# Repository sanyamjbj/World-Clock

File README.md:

# World_Clock_8085
An Intel 8085 microprocessor based device displaying the time of all the geographical time zones based on a user input.<br/>

Main_code.asm --------> The 8085 assembly language program.<br/>
Peripheral.brd -------> Board layout file for the I/O board. <br/>
Peripheral.sch -------> Circuit Schematic file for I/O board. <br/>
CPU.brd --------------> Board layout file for the 8085 CPU board. <br/>
world_clock_2.0.sch --> Circuit Schematic file for the 8085 CPU board. <br/>
All board and schematic files are made using Autodesk EAGLE. <br/>

[Image (a) of the Device](https://drive.google.com/file/d/1ZphsaR_vkj9hESxW5N7R6vfBDCEByzWG/view?usp=sharing)

[Image (b) of the Device](https://drive.google.com/file/d/1xtrZFzuJcVHUMF8EjI57J5fJ46bng3HB/view?usp=sharing)

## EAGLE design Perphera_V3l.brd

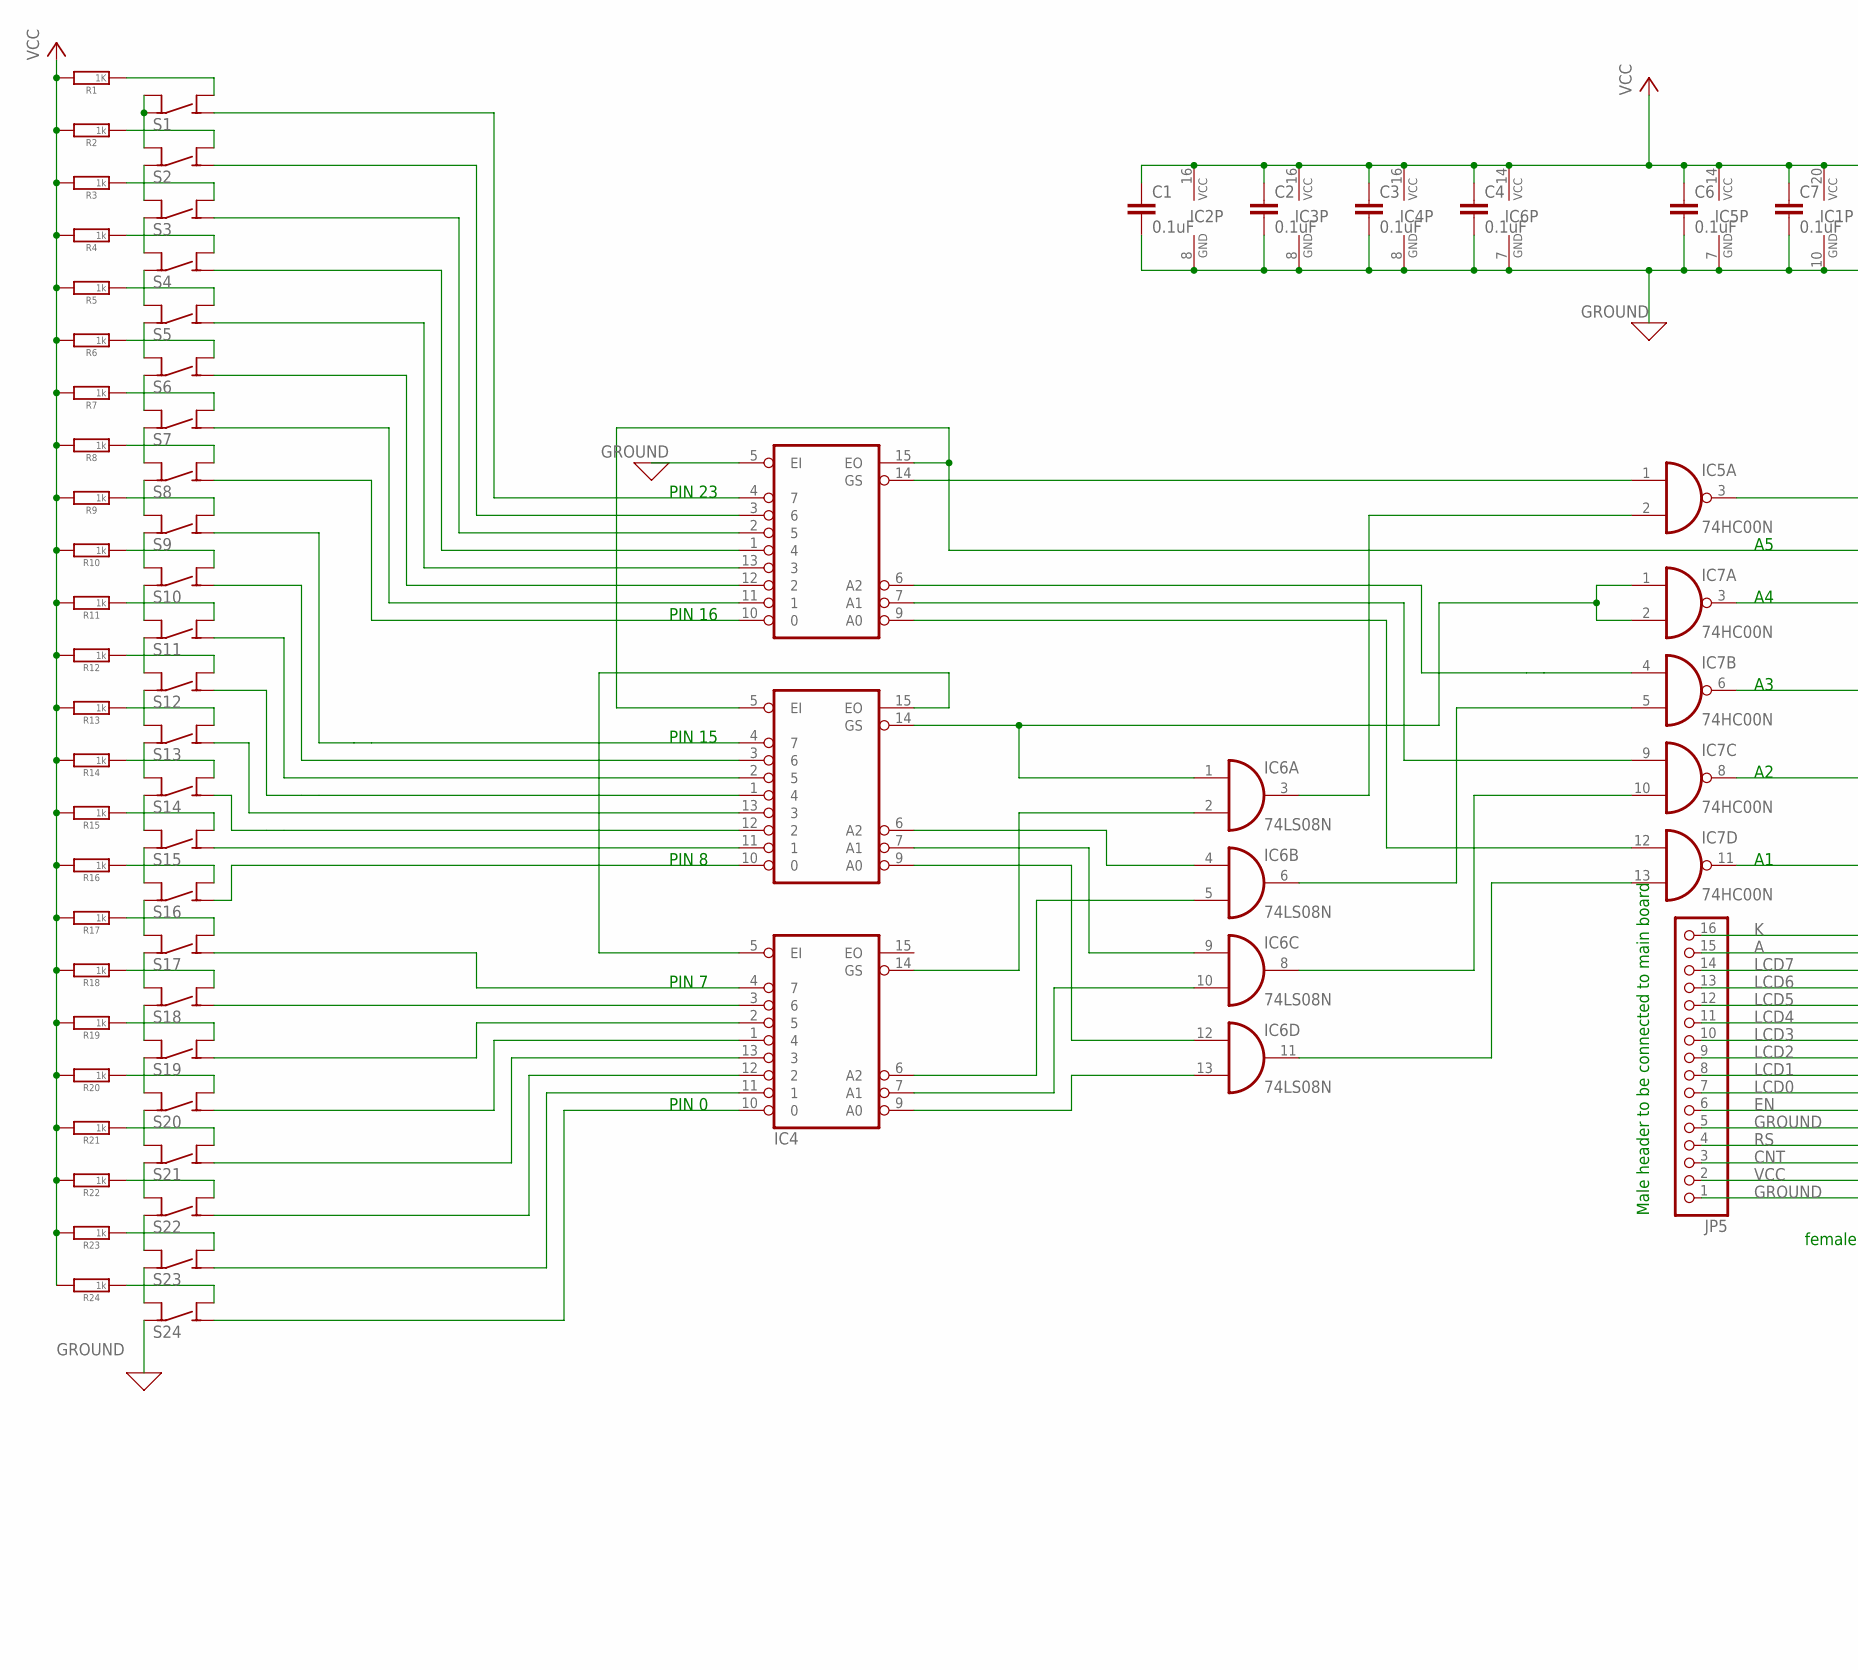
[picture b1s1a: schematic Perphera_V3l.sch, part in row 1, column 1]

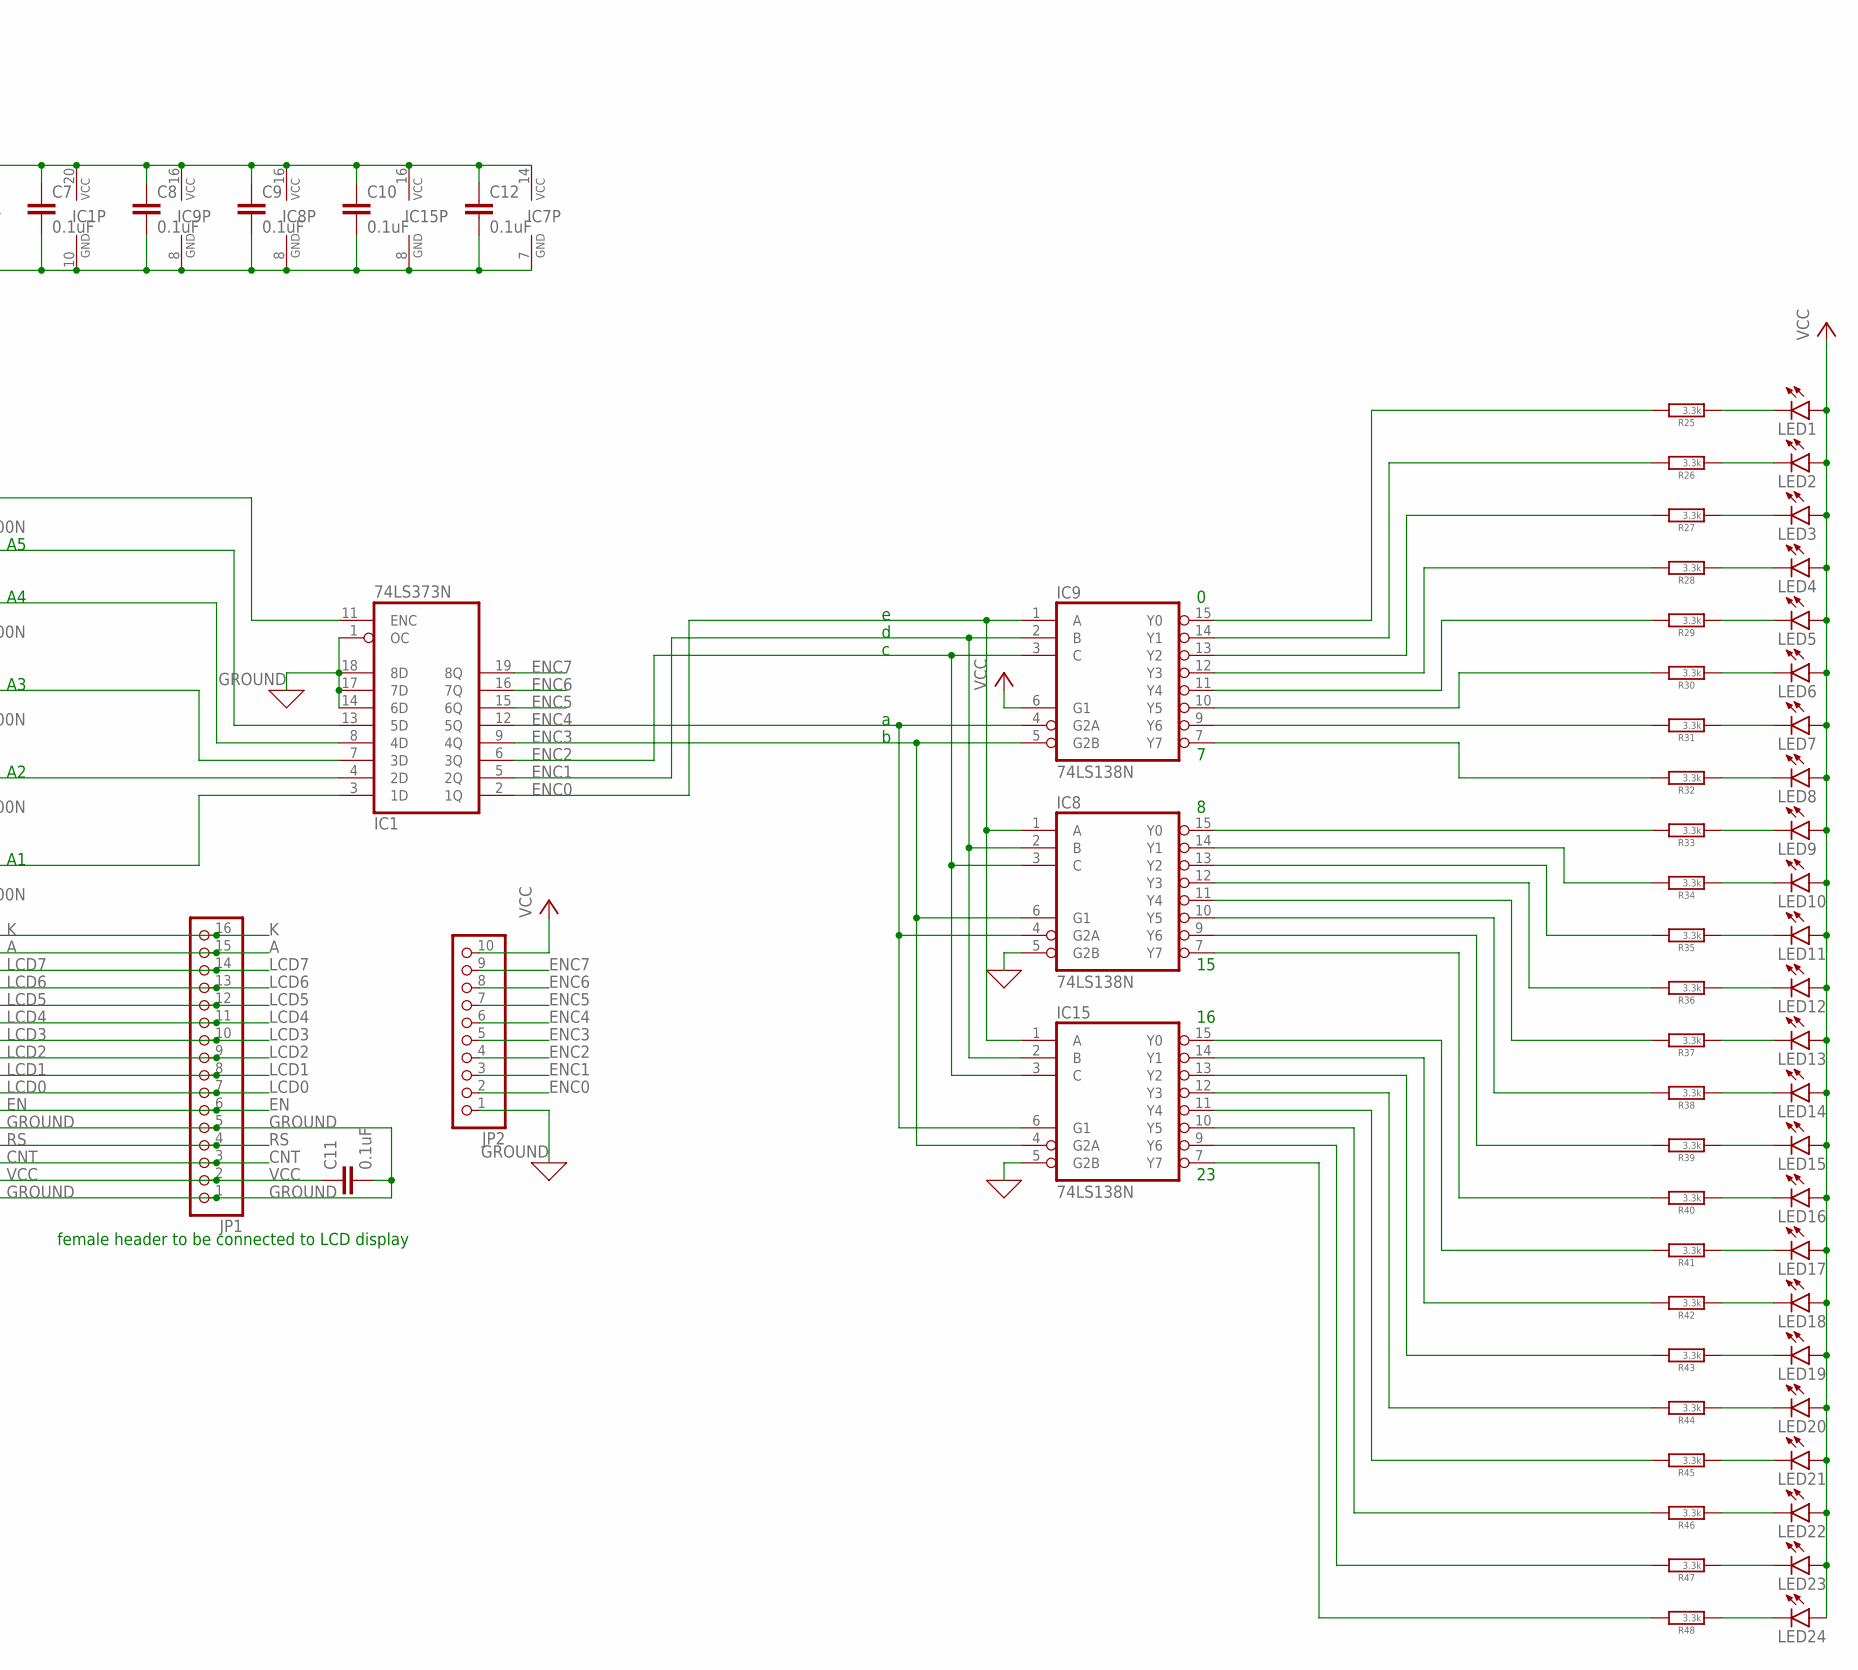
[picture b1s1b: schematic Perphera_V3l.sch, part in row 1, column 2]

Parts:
C1, C2, C3, C4, C6, C7, C8, C9, C10, C12: 0.1uF; C2.5-2
C11: 0.1uF; C025-025X050
IC1: 74LS373N; DIL20
IC2, IC3, IC4: 74HC148N; DIL16
IC5, IC7: 74HC00N; DIL14
IC6: 74LS08N; DIL14
IC8, IC9, IC15: 74LS138N; DIL16
JP1, JP5: PINHD-1X16; 1X16
JP2: PINHD-1X10; 1X10
LED1, LED2, LED3, LED4, LED5, LED6, LED7, LED8, LED9, LED10, LED11, LED12, LED13, LED14, LED15, LED16, LED17, LED18, LED19, LED20, LED21, LED22, LED23, LED24: LED5MM
R1: 1K; 1/6W(5MM)
R2, R3, R4, R5, R6, R7, R8, R9, R10, R11, R12, R13, R14, R15, R16, R17, R18, R19, R20, R21, R22, R23, R24: 1k; 1/6W(5MM)
R25, R26, R27, R28, R29, R30, R31, R32, R33, R34, R35, R36, R37, R38, R39, R40, R41, R42, R43, R44, R45, R46, R47, R48: 3.3k; 1/6W(5MM)
S1, S2, S3, S4, S5, S6, S7, S8, S9, S10, S11, S12, S13, S14, S15, S16, S17, S18, S19, S20, S21, S22, S23, S24: SPST4B3F-10XX; B3F-10XX

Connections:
A: JP1.15, JP5.15
CNT: JP1.3, JP5.3
EN: JP1.6, JP5.6
ENC0: IC1.2 (1Q), IC8.1 (A), IC9.1 (A), IC15.1 (A), JP2.2
ENC1: IC1.5 (2Q), IC8.2 (B), IC9.2 (B), IC15.2 (B), JP2.3
ENC2: IC1.6 (3Q), IC8.3 (C), IC9.3 (C), IC15.3 (C), JP2.4
ENC3: IC1.9 (4Q), IC8.6 (G1), IC9.5 (G2B), IC15.4 (G2A), JP2.5
ENC4: IC1.12 (5Q), IC8.4 (G2A), IC9.4 (G2A), IC15.6 (G1), JP2.6
ENC5: IC1.15 (6Q), JP2.7
ENC6: IC1.16 (7Q), JP2.8
ENC7: IC1.19 (8Q), JP2.9
GROUND: C1.2, C2.2, C3.2, C4.2, C6.2, C7.2, C8.2, C9.2, C10.2, C11.2, C12.2, IC1.1 (OC), IC1.10 (GND), IC1.14 (6D), IC1.17 (7D), IC1.18 (8D), IC2.5 (EI), IC2.8 (GND), IC3.8 (GND), IC4.8 (GND), IC5.7 (GND), IC6.7 (GND), IC7.7 (GND), IC8.5 (G2B), IC8.8 (GND), IC9.8 (GND), IC15.5 (G2B), IC15.8 (GND), JP1.1, JP1.5, JP2.1, JP5.1, JP5.5, S1.COM@1 (COM), S1.COM@2 (COM), S2.COM@1 (COM), S2.COM@2 (COM), S3.COM@1 (COM), S3.COM@2 (COM), S4.COM@1 (COM), S4.COM@2 (COM), S5.COM@1 (COM), S5.COM@2 (COM), S6.COM@1 (COM), S6.COM@2 (COM), S7.COM@1 (COM), S7.COM@2 (COM), S8.COM@1 (COM), S8.COM@2 (COM), S9.COM@1 (COM), S9.COM@2 (COM), S10.COM@1 (COM), S10.COM@2 (COM), S11.COM@1 (COM), S11.COM@2 (COM), S12.COM@1 (COM), S12.COM@2 (COM), S13.COM@1 (COM), S13.COM@2 (COM), S14.COM@1 (COM), S14.COM@2 (COM), S15.COM@1 (COM), S15.COM@2 (COM), S16.COM@1 (COM), S16.COM@2 (COM), S17.COM@1 (COM), S17.COM@2 (COM), S18.COM@1 (COM), S18.COM@2 (COM), S19.COM@1 (COM), S19.COM@2 (COM), S20.COM@1 (COM), S20.COM@2 (COM), S21.COM@1 (COM), S21.COM@2 (COM), S22.COM@1 (COM), S22.COM@2 (COM), S23.COM@1 (COM), S23.COM@2 (COM), S24.COM@1 (COM), S24.COM@2 (COM)
K: JP1.16, JP5.16
LCD0: JP1.7, JP5.7
LCD1: JP1.8, JP5.8
LCD2: JP1.9, JP5.9
LCD3: JP1.10, JP5.10
LCD4: JP1.11, JP5.11
LCD5: JP1.12, JP5.12
LCD6: JP1.13, JP5.13
LCD7: JP1.14, JP5.14
unnamed: IC2.10 (0), S8.NO@1 (NO)
unnamed: IC3.15 (EO), IC4.5 (EI)
unnamed: IC2.11 (1), S7.NO@1 (NO)
unnamed: IC2.9 (A0), IC7.12 (I0)
unnamed: IC2.12 (2), S6.NO@1 (NO)
unnamed: IC2.7 (A1), IC7.9 (I0)
unnamed: IC2.13 (3), S5.NO@1 (NO)
unnamed: IC2.1 (4), S4.NO@1 (NO)
unnamed: IC3.9 (A0), IC6.12 (I0)
unnamed: IC4.9 (A0), IC6.13 (I1)
unnamed: IC3.7 (A1), IC6.9 (I0)
unnamed: IC4.7 (A1), IC6.10 (I1)
unnamed: IC3.6 (A2), IC6.4 (I0)
unnamed: IC4.6 (A2), IC6.5 (I1)
unnamed: IC2.2 (5), S3.NO@1 (NO)
unnamed: IC6.11 (O), IC7.13 (I1)
unnamed: IC2.3 (6), S2.NO@1 (NO)
unnamed: IC6.8 (O), IC7.10 (I1)
unnamed: IC2.6 (A2), IC7.4 (I0)
unnamed: IC6.6 (O), IC7.5 (I1)
unnamed: IC4.4 (7), S17.NO@1 (NO)
unnamed: IC3.14 (GS), IC6.1 (I0), IC7.1 (I0), IC7.2 (I1)
unnamed: R1.1, S1.NO@2 (NO)
unnamed: R2.1, S2.NO@2 (NO)
unnamed: R3.1, S3.NO@2 (NO)
unnamed: R4.1, S4.NO@2 (NO)
unnamed: R5.1, S5.NO@2 (NO)
unnamed: R6.1, S6.NO@2 (NO)
unnamed: R7.1, S7.NO@2 (NO)
unnamed: R8.1, S8.NO@2 (NO)
unnamed: R9.1, S9.NO@2 (NO)
unnamed: R10.1, S10.NO@2 (NO)
unnamed: R11.1, S11.NO@2 (NO)
unnamed: R12.1, S12.NO@2 (NO)
unnamed: R13.1, S13.NO@2 (NO)
unnamed: R14.1, S14.NO@2 (NO)
unnamed: R15.1, S15.NO@2 (NO)
unnamed: R16.1, S16.NO@2 (NO)
unnamed: R17.1, S17.NO@2 (NO)
unnamed: R18.1, S18.NO@2 (NO)
unnamed: R19.1, S19.NO@2 (NO)
unnamed: R20.1, S20.NO@2 (NO)
unnamed: R21.1, S21.NO@2 (NO)
unnamed: R22.1, S22.NO@2 (NO)
unnamed: R23.1, S23.NO@2 (NO)
unnamed: R24.1, S24.NO@2 (NO)
unnamed: IC1.3 (1D), IC7.11 (O)
unnamed: IC1.4 (2D), IC7.8 (O)
unnamed: IC4.2 (5), S19.NO@1 (NO)
unnamed: IC4.1 (4), S20.NO@1 (NO)
unnamed: IC4.13 (3), S21.NO@1 (NO)
unnamed: IC4.12 (2), S22.NO@1 (NO)
unnamed: IC4.11 (1), S23.NO@1 (NO)
unnamed: IC4.10 (0), S24.NO@1 (NO)
unnamed: IC4.3 (6), S18.NO@1 (NO)
unnamed: IC1.7 (3D), IC7.6 (O)
unnamed: IC1.8 (4D), IC7.3 (O)
unnamed: IC4.14 (GS), IC6.2 (I1)
unnamed: IC2.14 (GS), IC5.1 (I0)
unnamed: IC2.4 (7), S1.NO@1 (NO)
unnamed: IC5.2 (I1), IC6.3 (O)
unnamed: IC3.4 (7), S9.NO@1 (NO)
unnamed: IC3.10 (0), S16.NO@1 (NO)
unnamed: IC3.11 (1), S15.NO@1 (NO)
unnamed: IC3.12 (2), S14.NO@1 (NO)
unnamed: IC3.13 (3), S13.NO@1 (NO)
unnamed: IC3.1 (4), S12.NO@1 (NO)
unnamed: IC3.2 (5), S11.NO@1 (NO)
unnamed: IC3.3 (6), S10.NO@1 (NO)
unnamed: IC1.11 (ENC), IC5.3 (O)
unnamed: IC1.13 (5D), IC2.15 (EO), IC3.5 (EI)
unnamed: IC9.15 (Y0), R25.2
unnamed: LED1.K (C), R25.1
unnamed: IC9.14 (Y1), R26.2
unnamed: IC9.13 (Y2), R27.2
unnamed: IC9.12 (Y3), R28.2
unnamed: IC9.11 (Y4), R29.2
unnamed: IC9.10 (Y5), R30.2
unnamed: IC9.9 (Y6), R31.2
unnamed: IC9.7 (Y7), R32.2
unnamed: IC8.15 (Y0), R33.2
unnamed: IC8.14 (Y1), R34.2
unnamed: IC8.13 (Y2), R35.2
unnamed: IC8.12 (Y3), R36.2
unnamed: IC8.11 (Y4), R37.2
unnamed: IC8.10 (Y5), R38.2
unnamed: IC8.9 (Y6), R39.2
unnamed: IC8.7 (Y7), R40.2
unnamed: IC15.15 (Y0), R41.2
unnamed: IC15.14 (Y1), R42.2
unnamed: IC15.13 (Y2), R43.2
unnamed: IC15.12 (Y3), R44.2
unnamed: IC15.11 (Y4), R45.2
unnamed: IC15.10 (Y5), R46.2
unnamed: IC15.9 (Y6), R47.2
unnamed: IC15.7 (Y7), R48.2
unnamed: LED2.K (C), R26.1
unnamed: LED3.K (C), R27.1
unnamed: LED4.K (C), R28.1
unnamed: LED5.K (C), R29.1
unnamed: LED6.K (C), R30.1
unnamed: LED7.K (C), R31.1
unnamed: LED8.K (C), R32.1
unnamed: LED9.K (C), R33.1
unnamed: LED10.K (C), R34.1
unnamed: LED11.K (C), R35.1
unnamed: LED12.K (C), R36.1
unnamed: LED13.K (C), R37.1
unnamed: LED14.K (C), R38.1
unnamed: LED15.K (C), R39.1
unnamed: LED16.K (C), R40.1
unnamed: LED17.K (C), R41.1
unnamed: LED18.K (C), R42.1
unnamed: LED19.K (C), R43.1
unnamed: LED20.K (C), R44.1
unnamed: LED21.K (C), R45.1
unnamed: LED22.K (C), R46.1
unnamed: LED23.K (C), R47.1
unnamed: LED24.K (C), R48.1
RS: JP1.4, JP5.4
VCC: C1.1, C2.1, C3.1, C4.1, C6.1, C7.1, C8.1, C9.1, C10.1, C11.1, C12.1, IC1.20 (VCC), IC2.16 (VCC), IC3.16 (VCC), IC4.16 (VCC), IC5.14 (VCC), IC6.14 (VCC), IC7.14 (VCC), IC8.16 (VCC), IC9.6 (G1), IC9.16 (VCC), IC15.16 (VCC), JP1.2, JP2.10, JP5.2, LED1.A, LED2.A, LED3.A, LED4.A, LED5.A, LED6.A, LED7.A, LED8.A, LED9.A, LED10.A, LED11.A, LED12.A, LED13.A, LED14.A, LED15.A, LED16.A, LED17.A, LED18.A, LED19.A, LED20.A, LED21.A, LED22.A, LED23.A, LED24.A, R1.2, R2.2, R3.2, R4.2, R5.2, R6.2, R7.2, R8.2, R9.2, R10.2, R11.2, R12.2, R13.2, R14.2, R15.2, R16.2, R17.2, R18.2, R19.2, R20.2, R21.2, R22.2, R23.2, R24.2

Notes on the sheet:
PIN 16
PIN 23
PIN 15
PIN 8
PIN 7
PIN 0
Male header to be connected to main board
female header to be connected to LCD display

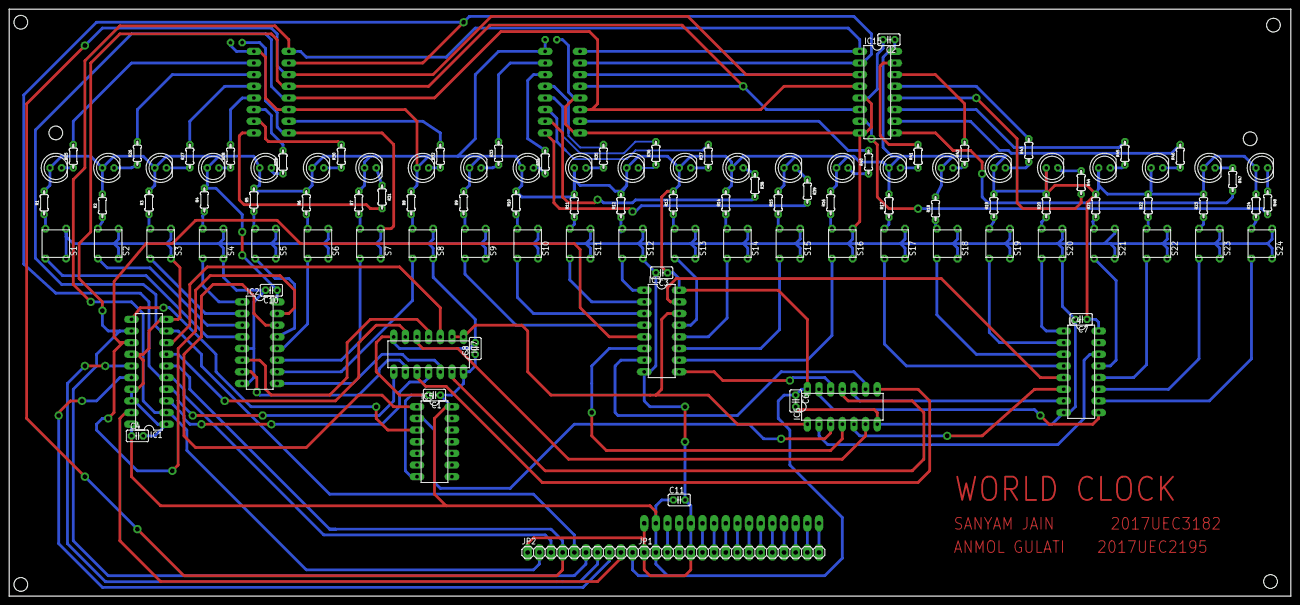
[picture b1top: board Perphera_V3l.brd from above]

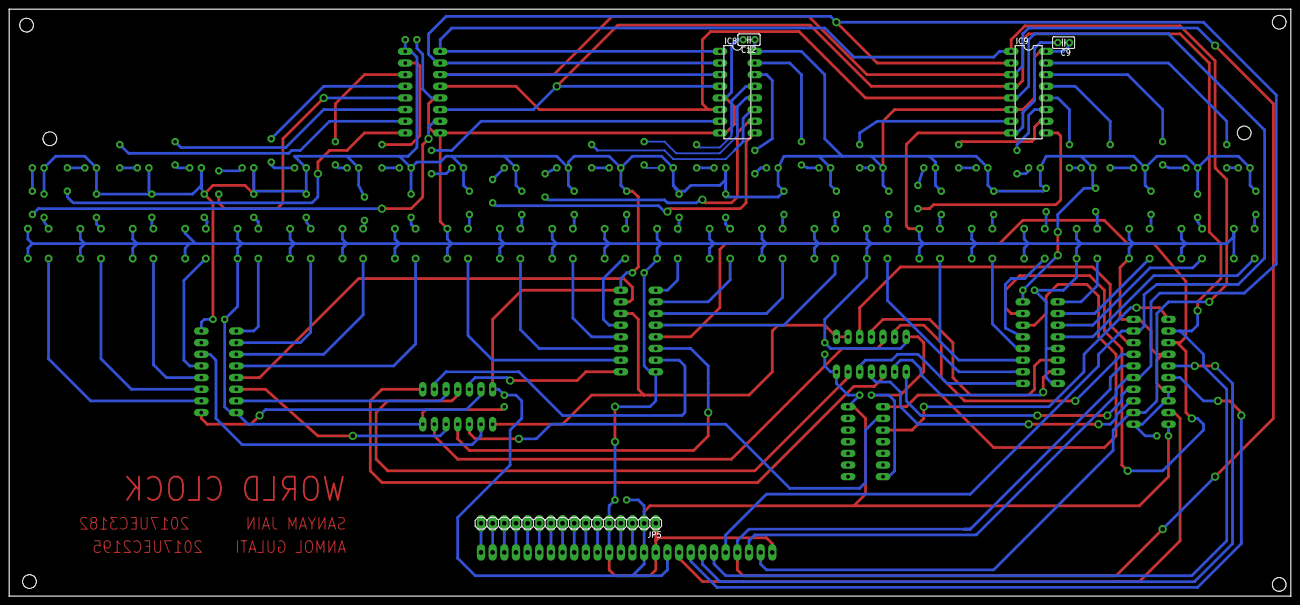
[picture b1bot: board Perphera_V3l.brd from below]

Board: 2 copper layers, 279.4 x 127.9 mm, 120 parts (5 on the bottom side), 142 nets.

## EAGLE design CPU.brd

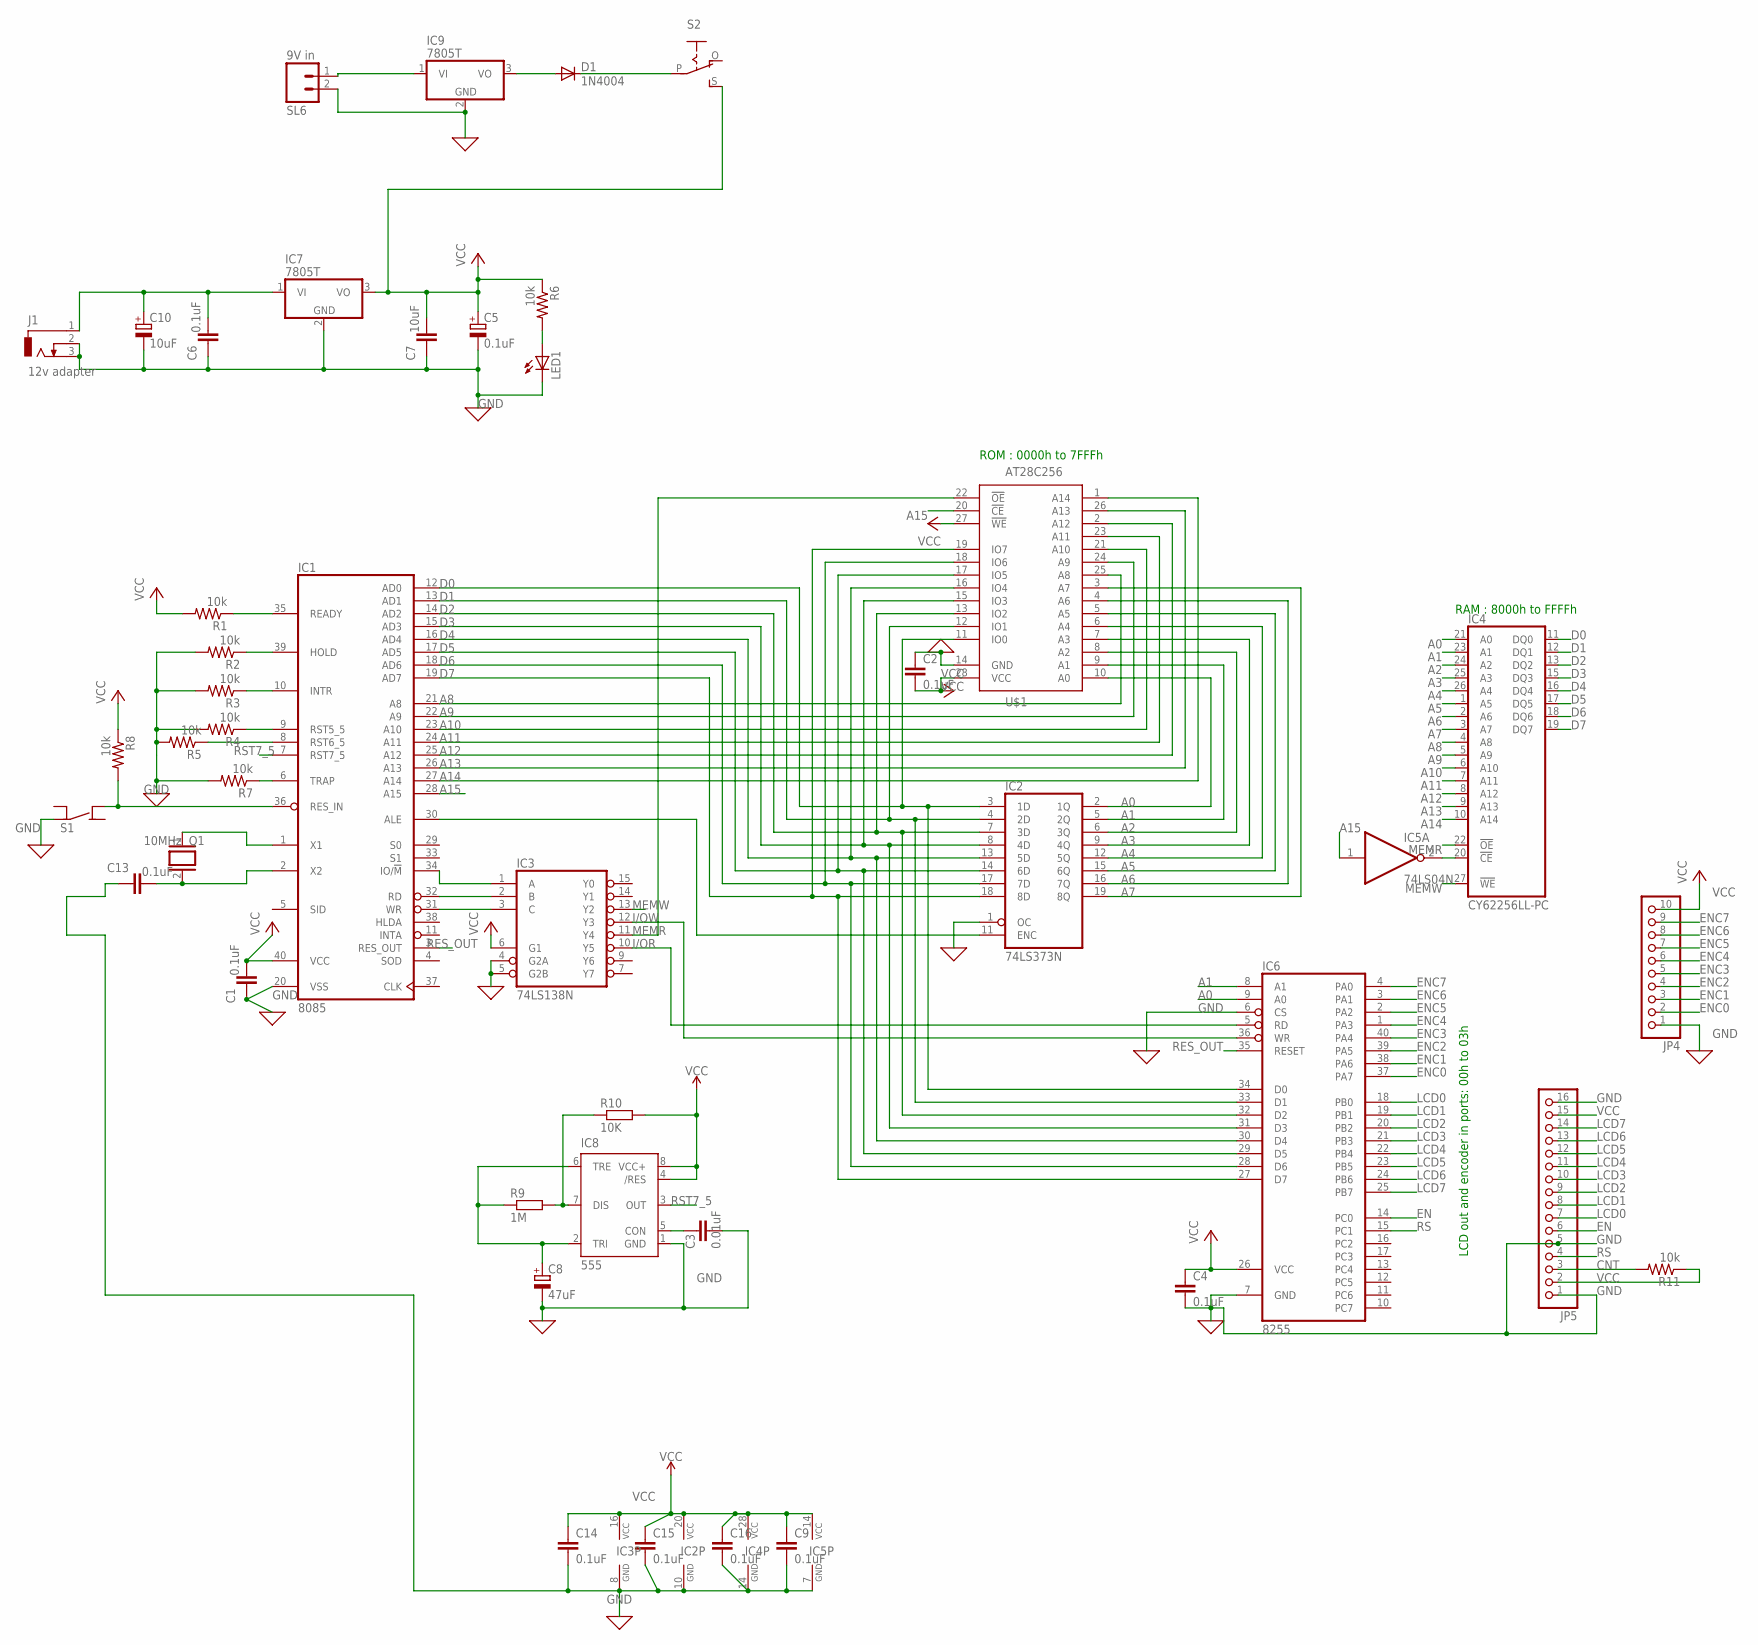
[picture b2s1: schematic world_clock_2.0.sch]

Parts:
C1, C2, C4, C6, C9, C13, C14, C15, C16: 0.1uF; C025-024X044
C3: 0.01uF; C2.5-2
C5: 0.1uF; E5-8,5
C7: 10uF; C025-024X044
C8: 47uF; E5-8,5
C10: 10uF; E5-8,5
D1: 1N4004; DO41-10
IC1: 8085; DIL40
IC2: 74LS373N; DIL20
IC3: 74LS138N; DIL16
IC4: CY62256LL-PC; DIL28-6
IC5: 74LS04N; DIL14
IC6: 8255; DIL40
IC7, IC9: 7805T; TO220H
IC8: 555; DIP08-KIT
J1: 12v adapter; DCJ0303
JP4: PINHD-1X10; 1X10
JP5: PINHD-1X16; 1X16
LED1: LED5MM
Q1: 10MHz; QS
R1, R2, R3, R4, R5, R6, R7, R8, R11: 10k; 0207/7
R9: 1M; 0204/5
R10: 10K; 0204/5
S1: SPST4B3F-10XX; B3F-10XX
S2: EG1218S; EG1218
SL6: 9V in; 02P
U$1: AT28C256; DIL28-6

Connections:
A0: IC2.2 (1Q), IC4.21 (A0), IC6.9 (A0), U$1.10 (A0)
A1: IC2.5 (2Q), IC4.23 (A1), IC6.8 (A1), U$1.9 (A1)
A2: IC2.6 (3Q), IC4.24 (A2), U$1.8 (A2)
A3: IC2.9 (4Q), IC4.25 (A3), U$1.7 (A3)
A4: IC2.12 (5Q), IC4.26 (A4), U$1.6 (A4)
A5: IC2.15 (6Q), IC4.1 (A5), U$1.5 (A5)
A6: IC2.16 (7Q), IC4.2 (A6), U$1.4 (A6)
A7: IC2.19 (8Q), IC4.3 (A7), U$1.3 (A7)
A8: IC1.21 (A8), IC4.4 (A8), U$1.25 (A8)
A9: IC1.22 (A9), IC4.5 (A9), U$1.24 (A9)
A10: IC1.23 (A10), IC4.6 (A10), U$1.21 (A10)
A11: IC1.24 (A11), IC4.7 (A11), U$1.23 (A11)
A12: IC1.25 (A12), IC4.8 (A12), U$1.2 (A12)
A13: IC1.26 (A13), IC4.9 (A13), U$1.26 (A13)
A14: IC1.27 (A14), IC4.10 (A14), U$1.1 (A14)
A15: IC1.28 (A15), IC5.1 (I), U$1.20 (!CE)
CNT: JP5.3, R11.2
D0: IC1.12 (AD0), IC2.3 (1D), IC4.11 (DQ0), IC6.34 (D0), U$1.11 (IO0)
D1: IC1.13 (AD1), IC2.4 (2D), IC4.12 (DQ1), IC6.33 (D1), U$1.12 (IO1)
D2: IC1.14 (AD2), IC2.7 (3D), IC4.13 (DQ2), IC6.32 (D2), U$1.13 (IO2)
D3: IC1.15 (AD3), IC2.8 (4D), IC4.15 (DQ3), IC6.31 (D3), U$1.15 (IO3)
D4: IC1.16 (AD4), IC2.13 (5D), IC4.16 (DQ4), IC6.30 (D4), U$1.16 (IO4)
D5: IC1.17 (AD5), IC2.14 (6D), IC4.17 (DQ5), IC6.29 (D5), U$1.17 (IO5)
D6: IC1.18 (AD6), IC2.17 (7D), IC4.18 (DQ6), IC6.28 (D6), U$1.18 (IO6)
D7: IC1.19 (AD7), IC2.18 (8D), IC4.19 (DQ7), IC6.27 (D7), U$1.19 (IO7)
EN: IC6.14 (PC0), JP5.6
ENC0: IC6.37 (PA7), JP4.2
ENC1: IC6.38 (PA6), JP4.3
ENC2: IC6.39 (PA5), JP4.4
ENC3: IC6.40 (PA4), JP4.5
ENC4: IC6.1 (PA3), JP4.6
ENC5: IC6.2 (PA2), JP4.7
ENC6: IC6.3 (PA1), JP4.8
ENC7: IC6.4 (PA0), JP4.9
GND: C1.1, C2.1, C3.2, C4.2, C5.-, C6.1, C7.1, C8.-, C9.2, C10.-, C13.1, C14.2, C15.2, C16.2, IC1.20 (VSS), IC2.1 (OC), IC2.10 (GND), IC3.4 (G2A), IC3.5 (G2B), IC3.8 (GND), IC4.14 (GND), IC5.7 (GND), IC6.6 (CS), IC6.7 (GND), IC7.2 (GND), IC8.1 (GND), IC9.2 (GND), J1.2, J1.3, JP4.1, JP5.1, JP5.5, JP5.16, LED1.K (C), R2.2, R3.2, R4.2, R5.2, R7.2, S1.COM@1 (COM), SL6.2, U$1.14 (GND)
I/OR: IC3.10 (Y5), IC6.5 (RD)
I/OW: IC3.12 (Y3), IC6.36 (WR)
LCD0: IC6.18 (PB0), JP5.7
LCD1: IC6.19 (PB1), JP5.8
LCD2: IC6.20 (PB2), JP5.9
LCD3: IC6.21 (PB3), JP5.10
LCD4: IC6.22 (PB4), JP5.11
LCD5: IC6.23 (PB5), JP5.12
LCD6: IC6.24 (PB6), JP5.13
LCD7: IC6.25 (PB7), JP5.14
MEMR: IC3.11 (Y4), IC4.22 (!OE), U$1.22 (!OE)
MEMW: IC3.13 (Y2), IC4.27 (!WE)
unnamed: C8.+, IC8.2 (TRI), IC8.6 (TRE), R9.1
unnamed: C6.2, C10.+, IC7.1 (VI), J1.1
unnamed: IC1.1 (X1), Q1.1
unnamed: C13.2, IC1.2 (X2), Q1.2
unnamed: IC1.35 (READY), R1.1
unnamed: IC1.39 (HOLD), R2.1
unnamed: IC8.7 (DIS), R9.2, R10.1
unnamed: IC1.10 (INTR), R3.1
unnamed: IC1.30 (ALE), IC2.11 (ENC)
unnamed: IC1.9 (RST5_5), R4.1
unnamed: IC1.8 (RST6_5), R5.1
unnamed: C3.1, IC8.5 (CON)
unnamed: IC1.6 (TRAP), R7.1
unnamed: IC9.1 (VI), SL6.1
unnamed: IC1.36 (RES_IN), R8.2, S1.NO@2 (NO)
unnamed: D1.A, IC9.3 (VO)
unnamed: D1.C, S2.P
unnamed: LED1.A, R6.2
unnamed: IC4.20 (!CE), IC5.2 (O)
unnamed: IC1.34 (IO/!M), IC3.1 (A)
unnamed: IC1.32 (RD), IC3.2 (B)
unnamed: IC1.31 (WR), IC3.3 (C)
RES_OUT: IC1.3 (RES_OUT), IC6.35 (RESET)
RS: IC6.15 (PC1), JP5.4
RST7_5: IC1.7 (RST7_5), IC8.3 (OUT)
VCC: C1.2, C2.2, C4.1, C5.+, C7.2, C9.1, C14.1, C15.1, C16.1, IC1.40 (VCC), IC2.20 (VCC), IC3.6 (G1), IC3.16 (VCC), IC4.28 (VCC), IC5.14 (VCC), IC6.26 (VCC), IC7.3 (VO), IC8.4 (/RES), IC8.8 (VCC+), JP4.10, JP5.2, JP5.15, R1.2, R6.1, R8.1, R10.2, R11.1, S2.S, U$1.27 (!WE), U$1.28 (VCC)

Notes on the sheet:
ROM : 0000h to 7FFFh
RAM : 8000h to FFFFh
LCD out and encoder in ports: 00h to 03h

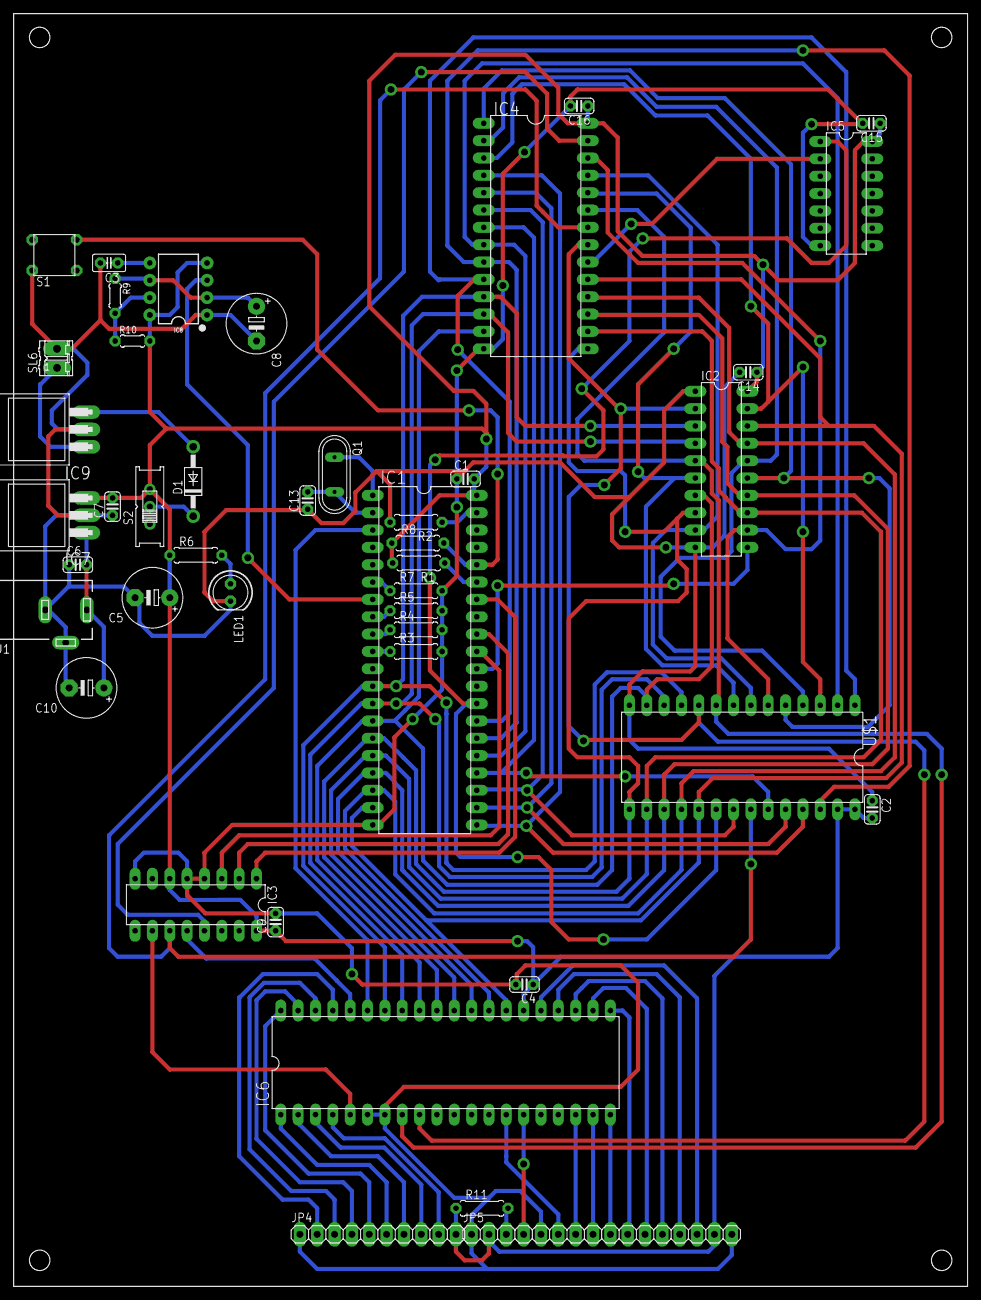
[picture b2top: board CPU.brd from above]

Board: 2 copper layers, 139.7 x 186.4 mm, 44 parts (0 on the bottom side), 73 nets.

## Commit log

2020-08-17 8085 Assembly Code
2020-08-17 Board File for the Peripheral I/O PCB
2020-08-17 Schematic for the Peripheral I/O PCB
2020-08-17 Board file for the 8085 CPU PCB
2020-08-17 Added file descriptions
2020-08-17 Added Images
2020-08-17 Added all images

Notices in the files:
parts and their libraries:
SparkFun-IC-Special-Function: Licensing: Creative Commons ShareAlike 4.0 International - https://creativecommons.org/licenses/by-sa/4.0
